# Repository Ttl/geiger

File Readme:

Open source Geiger counter

More information:
http://hforsten.com/i-made-a-geiger-counter.html

Includes code from LUFA:
http://www.fourwalledcubicle.com/LUFA.php

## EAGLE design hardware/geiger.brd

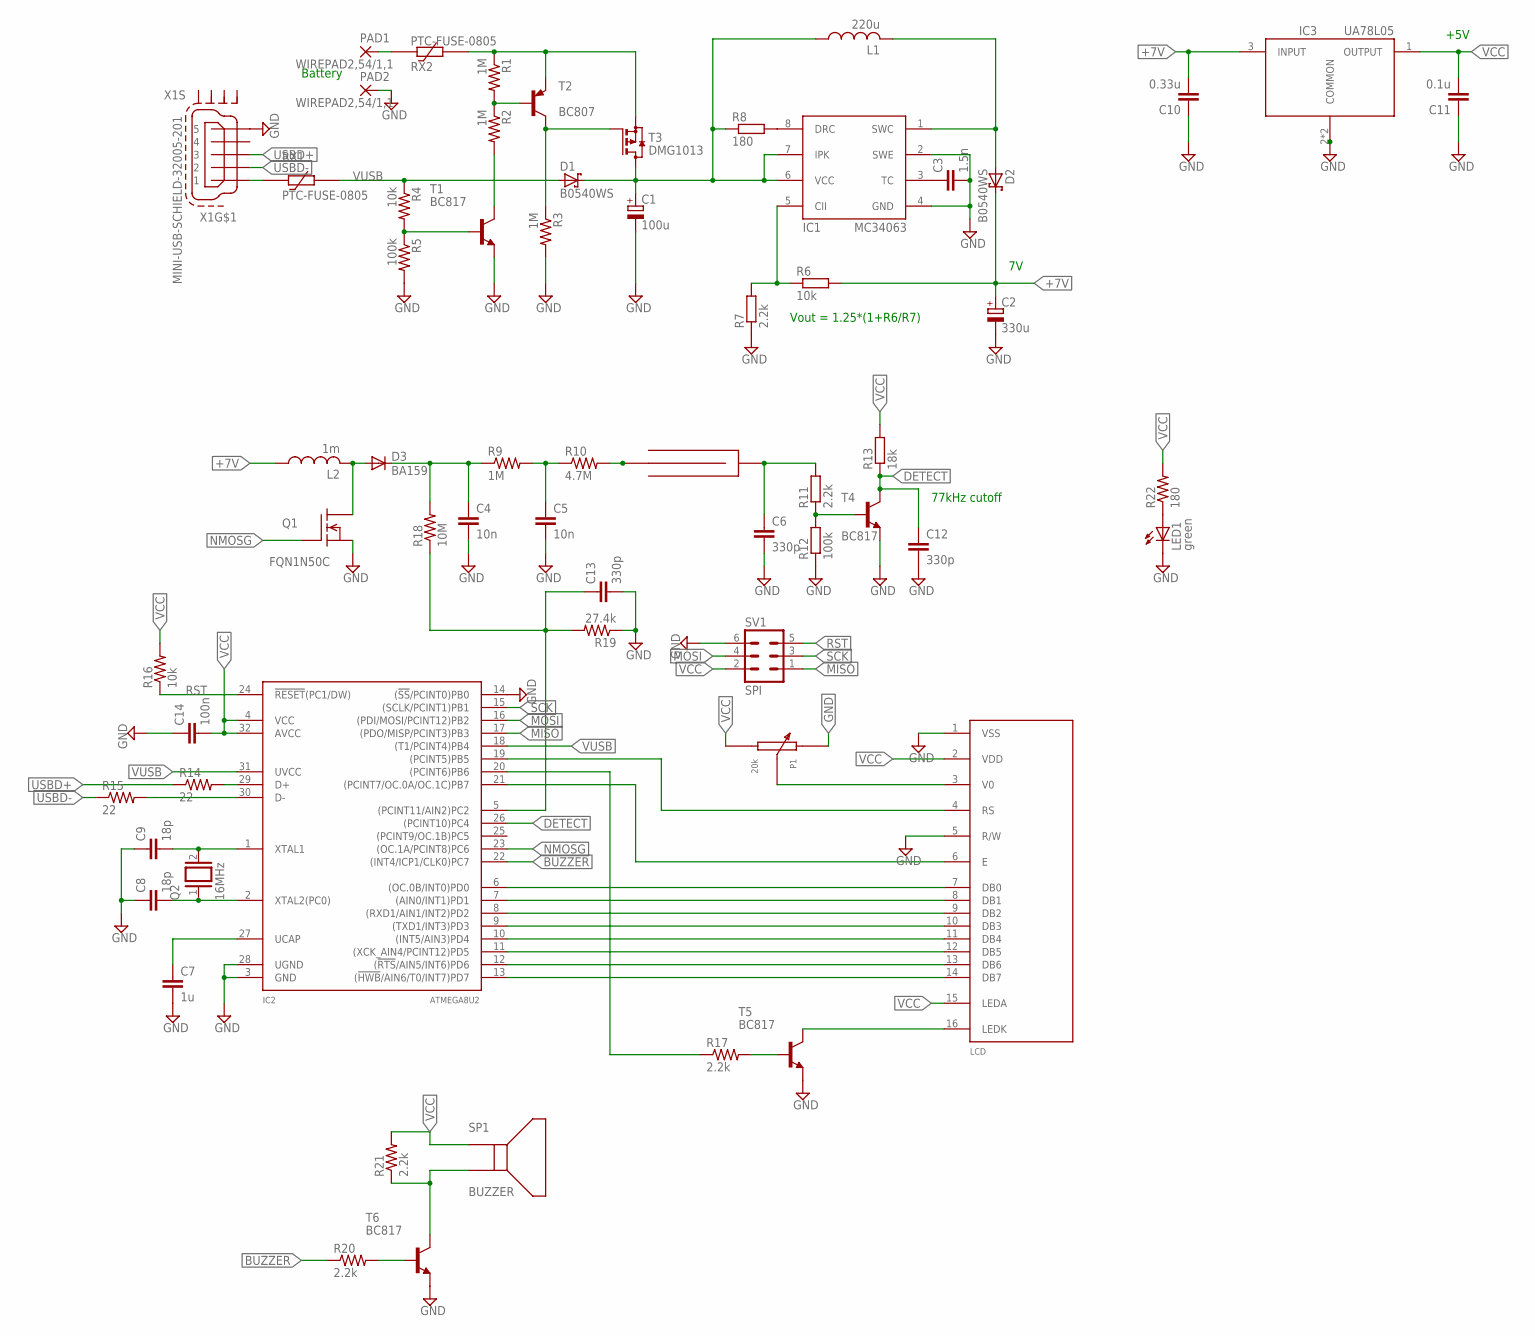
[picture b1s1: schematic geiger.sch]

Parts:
C1: 100u; E2,5-6
C2: 330u; E2,5-6
C3: 1.5n; C0603
C4, C5: 10n; C050-024X044
C6, C12, C13: 330p; C0603
C7: 1u; C0603
C8, C9: 18p; C0603
C10: 0.33u; C0603
C11: 0.1u; C0603
C14: 100n; C0603
D1, D2: B0540WS; SOD323-R
D3: BA159; DO41-10
G1: CI-22BG/SI-3BG; FUSE102074
IC1: MC34063; SO8
IC2: ATMEGA8U2; TQFP32-08
IC3: UA78L05; SOT89
L1: 220u; L8012
L2: 1m; L8012
LCD: TAYDA-LCD; LCD-PINOUT
LED1: green; CHIP-LED0603
P1: 20k; TRIMPOT
PAD1, PAD2: WIREPAD2,54/1,1; 2,54/1,1
Q1: FQN1N50C; TO92
Q2: 16MHz; QS
R1, R2, R3: 1M; R0603
R4, R6, R16: 10k; R0603
R5, R12: 100k; R0603
R7, R11, R17, R20, R21: 2.2k; R0603
R8, R22: 180; R0603
R9: 1M; 0207/7
R10: 4.7M; 0207/7
R13: 18k; R0603
R14, R15: 22; R0603
R18: 10M; 0207/7
R19: 27.4k; R0603
RX1, RX2: PTC-FUSE-0805; R0805
SP1: BUZZER
SV1: SPI; MA03-2
T1, T4, T5, T6: BC817; SOT23-BEC
T2: BC807; SOT23-BEC
T3: DMG1013; SOT323
X1: MINI-USB-SCHIELD-32005-201; 32005-201

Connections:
+7V: C2.+, C10.2, D2.C, IC3.3 (INPUT), L2.1, R6.2
BUZZER: IC2.22 ((INT4/ICP1/CLK0)PC7), R20.1
DETECT: C12.1, IC2.26 ((PCINT10)PC4), R13.1, T4.C
GND: C1.-, C2.-, C3.2, C4.2, C5.2, C6.2, C7.2, C8.1, C9.1, C10.1, C11.1, C12.2, C13.2, C14.1, IC1.2 (SWE), IC1.4 (GND), IC2.3 (GND), IC2.14 ((!SS!/PCINT0)PB0), IC2.28 (UGND), IC3.2 (COMMON), IC3.2@1 (COMMON), LCD.1 (VSS), LCD.5 (R/W), LED1.C, P1.P$2 (1), PAD2.1, Q1.1 (S), R3.2, R5.2, R7.1, R12.1, R19.1, SV1.6, T1.E, T4.E, T5.E, T6.E, X1.5
MISO: IC2.17 ((PDO/MISP/PCINT3)PB3), SV1.1
MOSI: IC2.16 ((PDI/MOSI/PCINT12)PB2), SV1.4
unnamed: R1.2, R2.1, T2.B
unnamed: R2.2, T1.C
unnamed: R3.1, T2.C, T3.2 (G)
unnamed: R1.1, RX2.2, T2.E, T3.3 (S)
unnamed: R4.2, R5.1, T1.B
unnamed: D3.A, L2.2, Q1.2 (D)
unnamed: C1.+, D1.C, IC1.6 (VCC), IC1.7 (IPK), L1.1, R8.1, T3.1 (D)
unnamed: IC1.5 (CII), R6.1, R7.2
unnamed: C4.1, D3.C, R9.1, R18.2
unnamed: C5.1, R9.2, R10.1
unnamed: IC1.8 (DRC), R8.2
unnamed: D2.A, IC1.1 (SWC), L1.2
unnamed: G1.A1 (A), G1.A2 (A), R10.2
unnamed: C3.1, IC1.3 (TC)
unnamed: R11.1, R12.2, T4.B
unnamed: C6.1, G1.C1 (C), G1.C2 (C), G1.C3 (C), G1.C4 (C), R11.2
unnamed: IC2.29 (D+), R14.2
unnamed: IC2.30 (D-), R15.2
unnamed: R21.1, SP1.P$2, T6.C
unnamed: RX1.1, X1.1
unnamed: C7.1, IC2.27 (UCAP)
unnamed: IC2.6 ((OC.0B/INT0)PD0), LCD.7 (DB0)
unnamed: C9.2, IC2.1 (XTAL1), Q2.2
unnamed: C8.2, IC2.2 (XTAL2(PC0)), Q2.1
unnamed: IC2.7 ((AIN0/INT1)PD1), LCD.8 (DB1)
unnamed: IC2.8 ((RXD1/AIN1/INT2)PD2), LCD.9 (DB2)
unnamed: IC2.9 ((TXD1/INT3)PD3), LCD.10 (DB3)
unnamed: IC2.10 ((INT5/AIN3)PD4), LCD.11 (DB4)
unnamed: IC2.11 ((XCK_AIN4/PCINT12)PD5), LCD.12 (DB5)
unnamed: IC2.12 ((!RTS!/AIN5/INT6)PD6), LCD.13 (DB6)
unnamed: IC2.13 ((!HWB!/AIN6/T0/INT7)PD7), LCD.14 (DB7)
unnamed: IC2.21 ((PCINT7/OC.0A/OC.1C)PB7), LCD.6 (E)
unnamed: PAD1.1, RX2.1
unnamed: IC2.19 ((PCINT5)PB5), LCD.4 (RS)
unnamed: LCD.3 (V0), P1.P$1 (WIPER)
unnamed: LCD.16 (LEDK), T5.C
unnamed: R17.2, T5.B
unnamed: IC2.20 ((PCINT6)PB6), R17.1
unnamed: C13.1, IC2.5 ((PCINT11/AIN2)PC2), R18.1, R19.2
unnamed: R20.2, T6.B
unnamed: LED1.A, R22.1
NMOSG: IC2.23 ((OC.1A/PCINT8)PC6), Q1.3 (G)
RST: IC2.24 (!RESET!(PC1/DW)), R16.1, SV1.5
SCK: IC2.15 ((SCLK/PCINT1)PB1), SV1.3
USBD+: R14.1, X1.3
USBD-: R15.1, X1.2
VCC: C11.2, C14.2, IC2.4 (VCC), IC2.32 (AVCC), IC3.1 (OUTPUT), LCD.2 (VDD), LCD.15 (LEDA), P1.P$3 (2), R13.2, R16.2, R21.2, R22.2, SP1.P$1, SV1.2
VUSB: D1.A, IC2.18 ((T1/PCINT4)PB4), IC2.31 (UVCC), R4.1, RX1.2

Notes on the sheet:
Battery
Vout = 1.25*(1+R6/R7)
77kHz cutoff
+5V

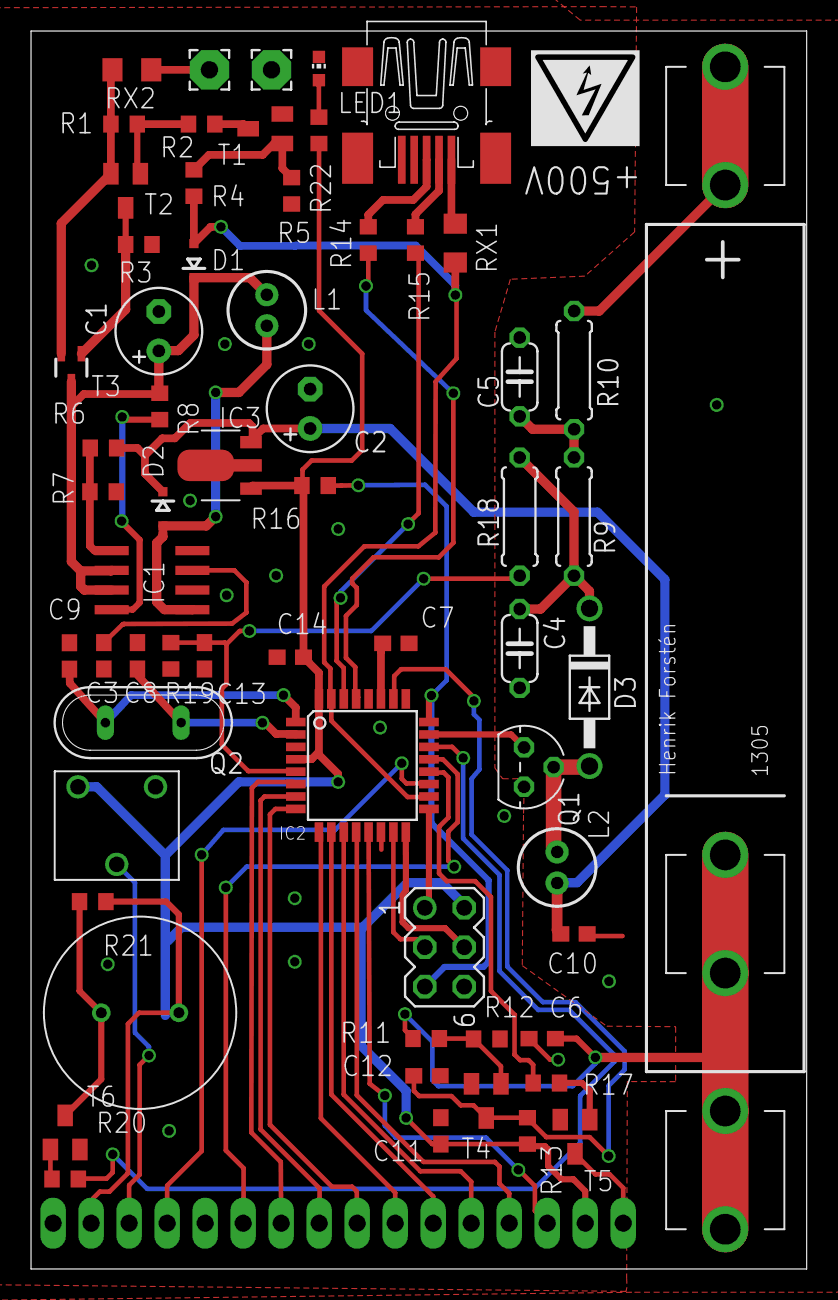
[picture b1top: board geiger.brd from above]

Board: 2 copper layers, 50.0 x 79.8 mm, 63 parts (0 on the bottom side), 54 nets.

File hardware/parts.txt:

Partlist

Exported from geiger.sch at 28.4.2013 10.19

EAGLE Version 6.4.0 Copyright (c) 1988-2013 CadSoft

Assembly variant: 

Part     Value                      Device                     Package      Library    Sheet

C1       100u                       CPOL-EUE2.5-6              E2,5-6       rcl        1
C2       330u                       CPOL-EUE2.5-6              E2,5-6       rcl        1
C3       1.5n                       C-EUC0603                  C0603        rcl        1
C4       10n                        C-EU050-024X044            C050-024X044 rcl        1
C5       10n                        C-EU050-024X044            C050-024X044 rcl        1
C6       330p                       C-EUC0603                  C0603        rcl        1
C7       1u                         C-EUC0603                  C0603        rcl        1
C8       18p                        C-EUC0603                  C0603        rcl        1
C9       18p                        C-EUC0603                  C0603        rcl        1
C10      0.33u                      C-EUC0603                  C0603        rcl        1
C11      0.1u                       C-EUC0603                  C0603        rcl        1
C12      330p                       C-EUC0603                  C0603        rcl        1
C13      330p                       C-EUC0603                  C0603        rcl        1
C14      100n                       C-EUC0603                  C0603        rcl        1
D1       B0540WS                    B0540WS                    SOD323-R     hf         1
D2       B0540WS                    B0540WS                    SOD323-R     hf         1
D3       BA159                      BA159                      DO41-10      hf         1
G1       CI-22BG/SI-3BG             CI-22BG/SI-3BG             FUSE102074   hf         1
IC1      MC34063                    MC34063                    SO8          hf         1
IC2      ATMEGA8U2                  ATMEGA8U2                  TQFP32-08    hf         1
IC3      UA78L05                    UA78L05                    SOT89        hf         1
L1       220u                       AIAP-01                    AIAP         hf         1
L2       1m                         BOURNS8012                 L8012        hf         1
LCD      TAYDA-LCD                  TAYDA-LCD                  LCD-PINOUT   hf         1
LED1     green                      LEDCHIP-LED0603            CHIP-LED0603 led        1
P1       20k                        TRIMPOT                    TRIMPOT      hf         1
Q1       FQN1N60C                   FQN1N60C                   TO92         hf         1
Q2       16MHz                      XTAL/S                     QS           hf         1
R1       1M                         R-US_R0603                 R0603        resistor   1
R2       1M                         R-US_R0603                 R0603        resistor   1
R3       1M                         R-US_R0603                 R0603        resistor   1
R4       10k                        R-US_R0603                 R0603        resistor   1
R5       100k                       R-US_R0603                 R0603        resistor   1
R6       10k                        R-EU_R0603                 R0603        resistor   1
R7       2.2k                       R-EU_R0603                 R0603        resistor   1
R8       180                        R-EU_R0603                 R0603        resistor   1
R9       1M                         R-US_0207/7                0207/7       rcl        1
R10      4.7M                       R-US_0207/7                0207/7       rcl        1
R11      2.2k                       R-EU_R0603                 R0603        resistor   1
R12      100k                       R-EU_R0603                 R0603        resistor   1
R13      18k                        R-EU_R0603                 R0603        resistor   1
R14      22                         R-US_R0603                 R0603        resistor   1
R15      22                         R-US_R0603                 R0603        resistor   1
R16      10k                        R-US_R0603                 R0603        resistor   1
R17      2.2k                       R-US_R0603                 R0603        resistor   1
R18      10M                        R-US_0207/7                0207/7       rcl        1
R19      27.4k                      R-US_R0603                 R0603        resistor   1
R20      2.2k                       R-US_R0603                 R0603        resistor   1
R21      2.2k                       R-US_R0603                 R0603        resistor   1
R22      180                        R-US_R0603                 R0603        resistor   1
RX1      PTC-FUSE-0805              PTC-FUSE-0805              R0805        hf         1
RX2      PTC-FUSE-0805              PTC-FUSE-0805              R0805        hf         1
SP1      BUZZER                     BUZZER                     BUZZER       hf         1
SV1      SPI                        MA03-2                     MA03-2       con-lstb   1
T1       BC817                      BC817-40-NPN-SOT23-BEC     SOT23-BEC    transistor 1
T2       BC807                      BC807-40-PNP-SOT23-BEC     SOT23-BEC    transistor 1
T3       DMG1013                    DMG1013                    SOT323       hf         1
T4       BC817                      BC817-40-NPN-SOT23-BEC     SOT23-BEC    transistor 1
T5       BC817                      BC817-40-NPN-SOT23-BEC     SOT23-BEC    transistor 1
T6       BC817                      BC817-40-NPN-SOT23-BEC     SOT23-BEC    transistor 1
X1       MINI-USB-SCHIELD-32005-201 MINI-USB-SCHIELD-32005-201 32005-201    hf         1

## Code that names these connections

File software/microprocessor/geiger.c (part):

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}

void setupHardware(void) {
    /* PC6 = NMOSG, PC7 = Buzzer */
    DDRC   = 0b11000000;
    DDRD   = 0b11111111;

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    /*  Initial duty cycle x/1024 */
    OCR1A  = 10;

    /*  Set detect interrupt on PC4(PCINT10) */
    PCMSK1 = 0b00000100;
    PCICR  = 0b00000010;

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    }
}

/*  Detect pin interrupt */
ISR(PCINT1_vect) {
    /*  Check if PC4 is 0 */
    if (bit_is_clear(PINC,4)) {
        count++;
        tick_pending = 1;
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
